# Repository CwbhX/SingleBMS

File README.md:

# Single BMS
![Product Name Screen Shot][product-screenshot]

## About
A BMS to provide accurate management of a lithium based battery pack with up to 16 cells in series.

[product-screenshot]: SingleBMS/images/SingleBMS.png

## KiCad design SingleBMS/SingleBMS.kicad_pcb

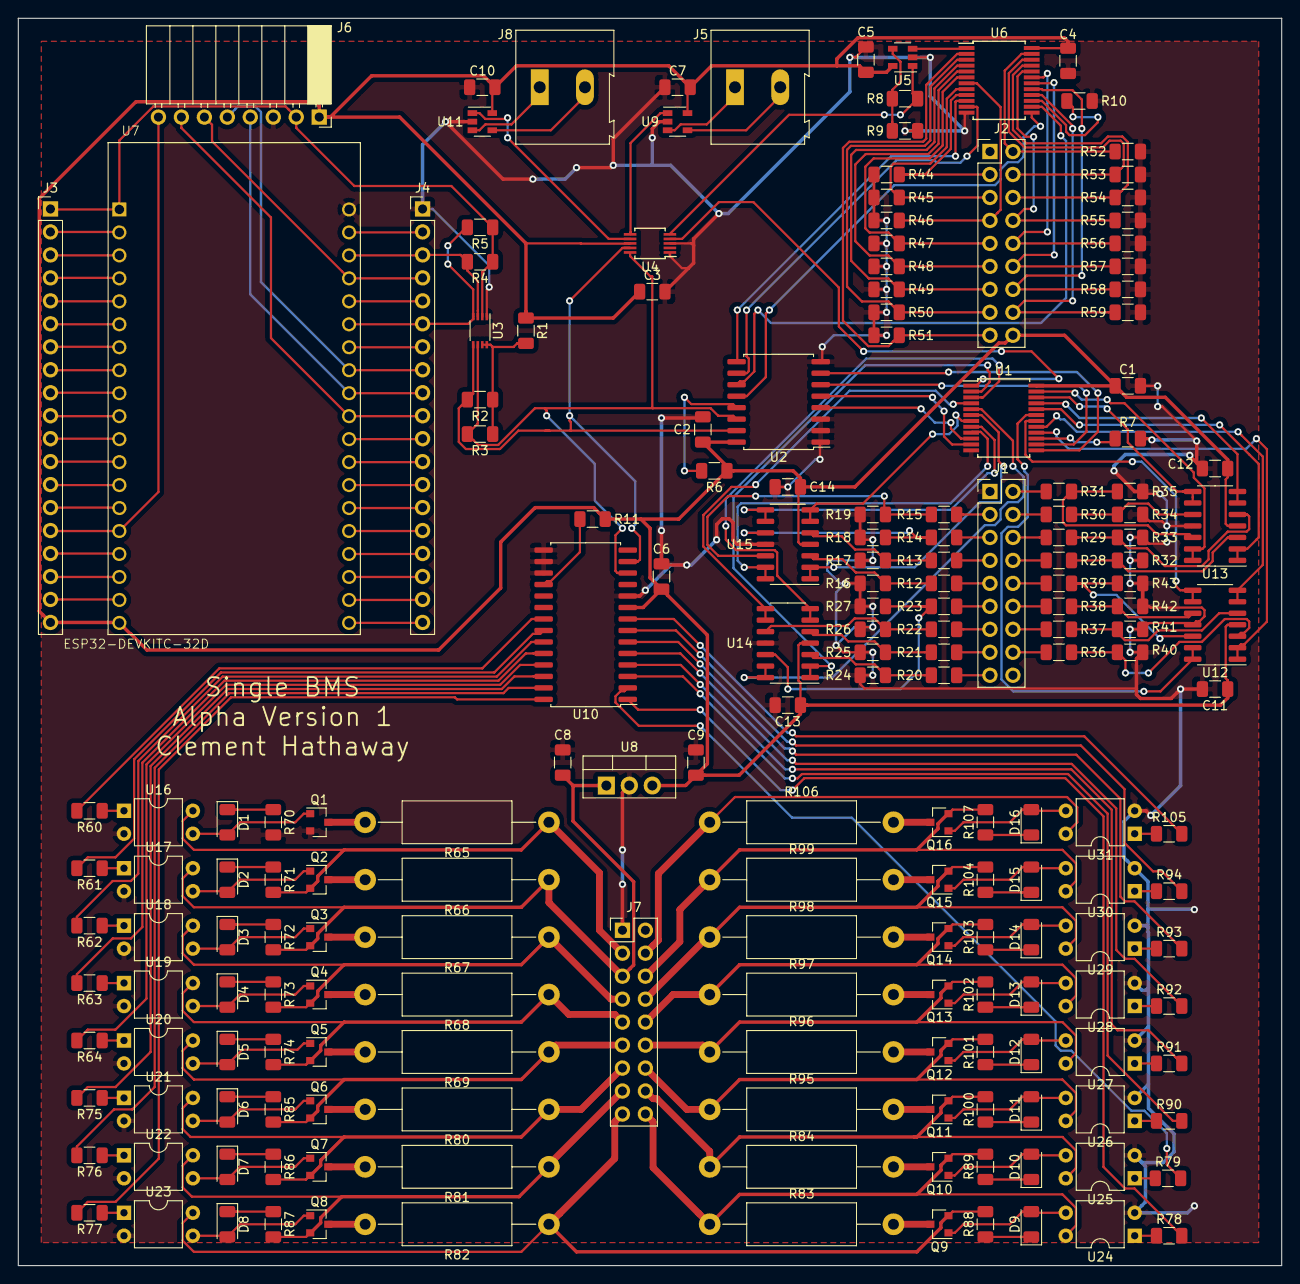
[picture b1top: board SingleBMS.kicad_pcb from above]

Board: 2 copper layers, 139.7 x 137.9 mm, 192 parts (0 on the bottom side), 223 nets.

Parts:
C1, C2, C3, C4, C5, C6, C7, C10, C11, C12, C13, C14: 0.01uF; C_1206_3216Metric
C8: 0.33uF; C_1206_3216Metric
C9: 0.1uF; C_1206_3216Metric
D1, D2, D3, D4, D5, D6, D7, D8, D9, D10, D11, D12, D13, D14, D15, D16: LED; LED_1206_3216Metric
J1, J2: Conn_02x09_Top_Bottom; PinHeader_2x09_P2.54mm_VerticalOrdering
J3, J4: Conn_01x19; PinHeader_1x19_P2.54mm_Vertical
J5, J8: Conn_01x02; TerminalBlock_Altech_AK300-2_P5.00mm
J6: Conn_01x08; PinSocket_1x08_P2.54mm_Horizontal
J7: Conn_02x09_Top_Bottom; PinHeader_2x09_P2.54mm_VerticalCounterClockwiseOrdering
Q1, Q2, Q3, Q4, Q5, Q6, Q7, Q8, Q9, Q10, Q11, Q12, Q13, Q14, Q15, Q16: 2N7002; SOT-23
R1: 200k; R_1206_3216Metric
R2, R3, R4, R5, R6, R7, R10, R11: 4.7k; R_1206_3216Metric
R8: 43k; R_1206_3216Metric
R9: 11k; R_1206_3216Metric
R12, R19: 300k; R_1206_3216Metric
R13, R31, R39: 240k; R_1206_3216Metric
R14, R16, R18: 100k; R_1206_3216Metric
R15: 1k; R_1206_3216Metric
R17, R23: 120k; R_1206_3216Metric
R20: 91k; R_1206_3216Metric
R21, R29, R37: 180k; R_1206_3216Metric
R22: 110k; R_1206_3216Metric
R24: 13K; R_1206_3216Metric
R25, R27, R32, R34, R35, R42: 30k; R_1206_3216Metric
R26: 22k; R_1206_3216Metric
R28: 330k; R_1206_3216Metric
R30, R36: 270k; R_1206_3216Metric
R33, R40: 18k; R_1206_3216Metric
R38: 390k; R_1206_3216Metric
R41: 13k; R_1206_3216Metric
R43: 20k; R_1206_3216Metric
R44, R45, R46, R47, R48, R49, R50, R51, R52, R53, R54, R55, R56, R57, R58, R59: 220k; R_1206_3216Metric
R60, R61, R62, R63, R64, R75, R76, R77, R78, R79, R90, R91, R92, R93, R94, R105: 510R; R_1206_3216Metric
R65, R66, R67, R68, R69, R80, R81, R82, R83, R84, R95, R96, R97, R98, R99, R106: 15R; R_Axial_DIN0414_L11.9mm_D4.5mm_P20.32mm_Horizontal
R70, R71, R72, R73, R74, R85, R86, R87, R88, R89, R100, R101, R102, R103, R104, R107: 270R; R_1206_3216Metric
U1, U6: CD74HC4067M; SSOP-24_5.3x8.2mm_P0.65mm
U2: PCF8574; SOIC-16W_7.5x10.3mm_P1.27mm
U3: PCA9306; VSSOP-8_2.3x2mm_P0.5mm
U4: ADS1115IDGS; MSOP-10_3x3mm_P0.5mm
U5: MCP6001-OT; SOT-23-5
U7: ESP32-DEVKITC-32D; MODULE_ESP32-DEVKITC-32D
U8: LM7805_TO220; TO-220-3_Vertical
U9, U11: INA194; SOT-23-5
U10: MCP23017_SP; SOIC-28W_7.5x17.9mm_P1.27mm
U12, U13, U14, U15: MCP6004; SOIC-14_3.9x8.7mm_P1.27mm
U16, U17, U18, U19, U20, U21, U22, U23, U24, U25, U26, U27, U28, U29, U30, U31: PC817; DIP-4_W7.62mm

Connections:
/Buffers16/B1: R15.2, R19.1, U15.12
/Buffers16/B2: R14.2, R18.1, U15.10
/Buffers16/B3: R13.2, R17.1, U15.5
/Buffers16/B4: R12.2, R16.1, U15.3
/Buffers16/B5: R23.2, R27.1, U14.12
/Buffers16/B6: R22.2, R26.1, U14.10
/Buffers16/B7: R21.2, R25.1, U14.5
/Buffers16/B8: R20.2, R24.1, U14.3
/Buffers16/B9: R31.2, R35.1, U13.12
/Buffers16/B10: R30.2, R34.1, U13.10
/Buffers16/B11: R29.2, R33.1, U13.5
/Buffers16/B12: R28.2, R32.1, U13.3
/Buffers16/B13: R39.2, R43.1, U12.12
/Buffers16/B14: R38.2, R42.1, U12.10
/Buffers16/B15: R37.2, R41.1, U12.5
/Buffers16/B16: R36.2, R40.1, U12.3
/Buffers16/BB1: U1.9, U15.13, U15.14
/Buffers16/BB2: U1.8, U15.8, U15.9
/Buffers16/BB3: U1.7, U15.6, U15.7
/Buffers16/BB4: U1.6, U15.1, U15.2
/Buffers16/BB5: U1.5, U14.13, U14.14
/Buffers16/BB6: U1.4, U14.8, U14.9
/Buffers16/BB7: U1.3, U14.6, U14.7
/Buffers16/BB8: U1.2, U14.1, U14.2
/Buffers16/BB9: U1.23, U13.13, U13.14
/Buffers16/BB10: U1.22, U13.8, U13.9
/Buffers16/BB11: U1.21, U13.6, U13.7
/Buffers16/BB12: U1.20, U13.1, U13.2
/Buffers16/BB13: U1.19, U12.13, U12.14
/Buffers16/BB14: U1.18, U12.8, U12.9
/Buffers16/BB15: U1.17, U12.6, U12.7
/Buffers16/BB16: U1.16, U12.1, U12.2
/SCL: R3.2, U2.14, U3.6, U4.10, U10.12
/SDA: R2.2, U2.15, U3.5, U4.9, U10.13
/Vcc33: J3.1, J6.2, R4.1, R5.1, U3.2, U7.1
/passiveBalance16/BCell1: J7.2, Q2.2, R65.1, R71.2, U16.4
/passiveBalance16/BCell2: C8.1, J7.3, Q3.2, R66.1, R72.2, U8.1, U17.4
/passiveBalance16/BCell3: J7.4, Q4.2, R67.1, R73.2, U18.4
/passiveBalance16/BCell4: J7.5, Q5.2, R68.1, R74.2, U19.4
/passiveBalance16/BCell5: J7.6, Q6.2, R69.1, R85.2, U20.4
/passiveBalance16/BCell6: J7.7, Q7.2, R80.1, R86.2, U21.4
/passiveBalance16/BCell7: J7.8, Q8.2, R81.1, R87.2, U22.4
/passiveBalance16/BCell8: J7.9, Q9.2, R82.1, R88.2, U23.4
/passiveBalance16/BCell9: J7.10, Q10.2, R83.1, R89.2, U24.4
/passiveBalance16/BCell10: J7.11, Q11.2, R84.1, R100.2, U25.4
/passiveBalance16/BCell11: J7.12, Q12.2, R95.1, R101.2, U26.4
/passiveBalance16/BCell12: J7.13, Q13.2, R96.1, R102.2, U27.4
/passiveBalance16/BCell13: J7.14, Q14.2, R97.1, R103.2, U28.4
/passiveBalance16/BCell14: J7.15, Q15.2, R98.1, R104.2, U29.4
/passiveBalance16/BCell15: J7.16, Q16.2, R99.1, R107.2, U30.4
/passiveBalance16/BCell16: J7.17, R106.1, U31.4
/passiveBalance16/Bal1: R60.2, U10.21
/passiveBalance16/Bal2: R61.2, U10.22
/passiveBalance16/Bal3: R62.2, U10.23
/passiveBalance16/Bal4: R63.2, U10.24
/passiveBalance16/Bal5: R64.2, U10.25
/passiveBalance16/Bal6: R75.2, U10.26
/passiveBalance16/Bal7: R76.2, U10.27
/passiveBalance16/Bal8: R77.2, U10.28
/passiveBalance16/Bal9: R78.2, U10.1
/passiveBalance16/Bal10: R79.2, U10.2
/passiveBalance16/Bal11: R90.2, U10.3
/passiveBalance16/Bal12: R91.2, U10.4
/passiveBalance16/Bal13: R92.2, U10.5
/passiveBalance16/Bal14: R93.2, U10.6
/passiveBalance16/Bal15: R94.2, U10.7
/passiveBalance16/Bal16: R105.2, U10.8
/tempDivider16/NTCReturn1: J2.2, R44.1, U6.9
/tempDivider16/NTCReturn2: J2.3, R45.1, U6.8
/tempDivider16/NTCReturn3: J2.4, R46.1, U6.7
/tempDivider16/NTCReturn4: J2.5, R47.1, U6.6
/tempDivider16/NTCReturn5: J2.6, R48.1, U6.5
/tempDivider16/NTCReturn6: J2.7, R49.1, U6.4
/tempDivider16/NTCReturn7: J2.8, R50.1, U6.3
/tempDivider16/NTCReturn8: J2.9, R51.1, U6.2
/tempDivider16/NTCReturn9: J2.10, R52.1, U6.23
/tempDivider16/NTCReturn10: J2.11, R53.1, U6.22
/tempDivider16/NTCReturn11: J2.12, R54.1, U6.21
/tempDivider16/NTCReturn12: J2.13, R55.1, U6.20
/tempDivider16/NTCReturn13: J2.14, R56.1, U6.19
/tempDivider16/NTCReturn14: J2.15, R57.1, U6.18
/tempDivider16/NTCReturn15: J2.16, R58.1, U6.17
/tempDivider16/NTCReturn16: J2.17, R59.1, U6.16
/voltageDivider16/VBat1: J1.2, R15.1
/voltageDivider16/VBat2: J1.3, R14.1
/voltageDivider16/VBat3: J1.4, R13.1
/voltageDivider16/VBat4: J1.5, R12.1
/voltageDivider16/VBat5: J1.6, R23.1
/voltageDivider16/VBat6: J1.7, R22.1
/voltageDivider16/VBat7: J1.8, R21.1
/voltageDivider16/VBat8: J1.9, R20.1
/voltageDivider16/VBat9: J1.10, R31.1
/voltageDivider16/VBat10: J1.11, R30.1
/voltageDivider16/VBat11: J1.12, R29.1
/voltageDivider16/VBat12: J1.13, R28.1
/voltageDivider16/VBat13: J1.14, R39.1
/voltageDivider16/VBat14: J1.15, R38.1
/voltageDivider16/VBat15: J1.16, R37.1
/voltageDivider16/VBat16: J1.17, R36.1
GND: C1.2, C2.2, C3.2, C4.1, C5.1, C6.2, C7.1, C8.2, C9.2, C10.1, C11.2, C12.2, C13.2, C14.2, J1.1, J4.1, J6.3, J7.1, Q1.2, R7.2, R9.1, R10.2, R16.2, R17.2, R18.2, R19.2, R24.2, R25.2, R26.2, R27.2, R32.2, R33.2, R34.2, R35.2, R40.2, R41.2, R42.2, R43.2, R44.2, R45.2, R46.2, R47.2, R48.2, R49.2, R50.2, R51.2, R52.2, R53.2, R54.2, R55.2, R56.2, R57.2, R58.2, R59.2, R70.2, U1.12, U2.1, U2.2, U2.3, U2.8, U3.1, U4.1, U4.3, U5.2, U6.12, U7.20, U8.2, U9.2, U10.10, U10.15, U10.16, U10.17, U11.2, U12.11, U13.11, U14.11, U15.11, U16.2, U17.2, U18.2, U19.2, U20.2, U21.2, U22.2, U23.2, U24.2, U25.2, U26.2, U27.2, U28.2, U29.2, U30.2, U31.2
unnamed: D1.1, R70.1
unnamed: D1.2, Q1.1, U16.3
unnamed: D2.1, R71.1
unnamed: D2.2, Q2.1, U17.3
unnamed: D3.1, R72.1
unnamed: D3.2, Q3.1, U18.3
unnamed: D4.1, R73.1
unnamed: D4.2, Q4.1, U19.3
unnamed: D5.1, R74.1
unnamed: D5.2, Q5.1, U20.3
unnamed: D6.1, R85.1
unnamed: D6.2, Q6.1, U21.3
unnamed: D7.1, R86.1
unnamed: D7.2, Q7.1, U22.3
unnamed: D8.1, R87.1
unnamed: D8.2, Q8.1, U23.3
unnamed: D9.1, R88.1
unnamed: D9.2, Q9.1, U24.3
unnamed: D10.1, R89.1
unnamed: D10.2, Q10.1, U25.3
unnamed: D11.1, R100.1
unnamed: D11.2, Q11.1, U26.3
unnamed: D12.1, R101.1
unnamed: D12.2, Q12.1, U27.3
unnamed: D13.1, R102.1
unnamed: D13.2, Q13.1, U28.3
unnamed: D14.1, R103.1
unnamed: D14.2, Q14.1, U29.3
unnamed: D15.1, R104.1
unnamed: D15.2, Q15.1, U30.3
unnamed: D16.1, R107.1
unnamed: D16.2, Q16.1, U31.3
unnamed: J3.2, U7.2
unnamed: J3.3, U7.3
unnamed: J3.4, U7.4
unnamed: J3.5, U7.5
unnamed: J3.6, U7.6
unnamed: J3.7, U7.7
unnamed: J3.8, U7.8
unnamed: J3.9, U7.9
unnamed: J3.10, U7.10
unnamed: J3.11, U7.11
unnamed: J3.12, U7.12
unnamed: J3.13, U7.13
unnamed: J3.14, U7.14
unnamed: J3.15, J6.8, U7.15
unnamed: J3.16, U7.16
unnamed: J3.17, U7.17
unnamed: J3.18, U7.18
unnamed: J4.2, U7.21
unnamed: J4.3, R4.2, U3.3, U7.22
unnamed: J4.4, J6.6, U7.23
unnamed: J4.5, U7.24
unnamed: J4.6, R5.2, U3.4, U7.25
unnamed: J4.7, U7.26
unnamed: J4.8, J6.5, U7.27
unnamed: J4.9, J6.4, U7.28
unnamed: J4.10, J6.7, U7.29
unnamed: J4.11, U7.30
unnamed: J4.12, U7.31
unnamed: J4.13, U7.32
unnamed: J4.14, U7.33
unnamed: J4.15, U7.34
unnamed: J4.16, U7.35
unnamed: J4.17, U7.36
unnamed: J4.18, U7.37
unnamed: J4.19, U7.38
unnamed: J5.1, U9.3
unnamed: J5.2, U9.4
unnamed: J8.1, U11.3
unnamed: J8.2, U11.4
unnamed: Q1.3, R65.2
unnamed: Q2.3, R66.2
unnamed: Q3.3, R67.2
unnamed: Q4.3, R68.2
unnamed: Q5.3, R69.2
unnamed: Q6.3, R80.2
unnamed: Q7.3, R81.2
unnamed: Q8.3, R82.2
unnamed: Q9.3, R83.2
unnamed: Q10.3, R84.2
unnamed: Q11.3, R95.2
unnamed: Q12.3, R96.2
unnamed: Q13.3, R97.2
unnamed: Q14.3, R98.2
unnamed: Q15.3, R99.2
unnamed: Q16.3, R106.2
unnamed: R1.2, R2.1, R3.1, U3.7, U3.8
unnamed: R6.2, U2.13
unnamed: R7.1, U1.15
unnamed: R8.1, R9.2, U5.4
unnamed: R8.2, U4.5, U5.1
unnamed: R10.1, U6.15
unnamed: R11.2, U10.18
unnamed: R60.1, U16.1
unnamed: R61.1, U17.1
unnamed: R62.1, U18.1
unnamed: R63.1, U19.1
unnamed: R64.1, U20.1
unnamed: R75.1, U21.1
unnamed: R76.1, U22.1
unnamed: R77.1, U23.1
unnamed: R78.1, U24.1
unnamed: R79.1, U25.1
unnamed: R90.1, U26.1
unnamed: R91.1, U27.1
unnamed: R92.1, U28.1
unnamed: R93.1, U29.1
unnamed: R94.1, U30.1
unnamed: R105.1, U31.1
unnamed: U1.1, U4.4
unnamed: U1.10, U2.4
unnamed: U1.11, U2.5
unnamed: U1.13, U2.7
unnamed: U1.14, U2.6
unnamed: U2.9, U6.10
unnamed: U2.10, U6.11
unnamed: U2.11, U6.14
unnamed: U2.12, U6.13
unnamed: U4.6, U9.1
unnamed: U5.3, U6.1
unnamed: U4.7, U11.1
Vcc: C1.1, C2.1, C3.1, C4.2, C5.2, C6.1, C7.2, C9.1, C10.2, C11.1, C12.1, C13.1, C14.1, J2.18, J3.19, J6.1, R1.1, R6.1, R11.1, U1.24, U2.16, U4.8, U5.5, U6.24, U7.19, U8.3, U9.5, U10.9, U11.5, U12.4, U13.4, U14.4, U15.4

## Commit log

2019-11-13 added cells
2019-11-14 added 16 cells and op amps
2019-11-14 Changed voltage dividers and added buffers and analogue mux
    Votlage dividers now all go down to 4.0 volts to work better with ADS1115 with a gain of 1, which means for the highest (16th) cell we can get 1142 levels of resolution of a range from 4.2v to 3.0v
2019-11-16 added more chips
2019-11-18 ting
2019-11-19 added subsheets
2019-11-19 Added subsheets for more components
2019-11-19 Added balance subsheet
2019-11-19 Made Temp Sensors more linear
2019-11-19 Added Labels
2019-11-19 Replaced LM324 with MCP6004
2019-11-19 Added current sensing stages
2019-11-25 Added decoupling caps and ESP32 dev board
2019-11-28 Replaced current sense opamp with INA194
2019-11-28 Replaced MCP6004 with 6001
2019-11-28 Added ESP32 WROOM dev board
2019-11-28 Setup I2C datalines and addresses
2019-11-28 Wired up ESP32 and SD Card reader
2019-11-28 Added labels to components
2019-11-28 Created PDF
2019-11-28 Replaced BS150 with 2n7000
2019-11-28 annotation
2019-11-29 Assigned footprints mainly matching JLCPCB parts lists & generated netlist
2019-12-09 idk i forget but its probably good
2019-12-24 Updated schematic with Vcc Globals, finished PCB layout, added screenshots
2019-12-26 Added parts for SMT, fixed voltage dividers, fixed footprint sizes
2019-12-26 Generated gerber files
2020-01-04 Updated resisor values, mostly in voltage divider
2020-01-10 Fixed Schematic I2C Pullup bug and address conflicts but PCB not updated
    Fixed pullup issue on the 5 volt line, fixed address of PCF8574 from 0x20 to 0x21 to not conflict with the MCP23017 (which is at 0x20), but is really confusing since TI states a seperate Read/Write a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
2020-01-10 Updated schematic with link to 8-bit addressing for PCF8574
